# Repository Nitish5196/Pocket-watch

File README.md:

# Pocket Watch- KN
Its a mini pocket watch with a round display , a vibrating motor , a battery and a xiao esp32-C6 . and the best part? it charges wirelesslyyyyy
ikr so cool . so i designed the pcb in kicad , the case in fusion 360 and the firmware in vs code and ardunio ide oh about the firmware i forgot to tell you wht it does.
### Firmware:
- it has a deep sleep mode so most of the time its sleeping to conserve battery , it wakes up at when you shake it aggressively 
- when it turns on in the mrng and it broadcasts its own local wifi , you connect to it , open the webpage and a prompt pops up asking for day order or holiday
once you enter tht , it will show the tabular form of the time table of the day and sends a message to the watch and turns off
- during normal time the screen stays black and shows nothing , but you can shake to wake it up make it show the time and current/upcoming class.
- automatically 5mins before and at the start of the class it lights up and notifies you by turning on and vibrating
- Right before i leave for school it turns on and once i submit the day order the wifi turns off and it goes back to sleep
- THIS IS DESIGNED ACCORDING TO MY SCHOOL TIME TABLE SO YOU SHOULD PROBABLY MAKE CHANGES TO THE FIRMWARE IF YOU'RE PLANNING TO USE IT 
## PCB 

## Case (will make changes once the component's size are measured)

## BOM
## Bill of Materials (BOM)

| Part | Quantity | Total Cost(USD) | Vendor | Link |
|---|---:|---:|---|---|
| Flat 1034 Mobile Phone Vibrator Motor | 1 | $0.31 | Robu | [link](https://robu.in/product/flat-1027-mobile-phone-vibration-motor/) |
| STMicroelectronics LIS3DH 3-Axis Digital Accelerometer | 1 | $2.7 | Robocraze | [link](https://robocraze.com/products/7semi-lis3dh-triple-axis-mems-accelerometer-breakout-module-i2c-spi?variant=52662486434016) |
| GoldenMorning GC9A01P 1.28" 240×240 SPI Round Display | 1 | $5.06 | Robu | [link](https://robu.in/product/goldenmorning-gc9a01-7p-240x240-spi-1-28-inch-round-display-module/) |
| 2N2222 NPN Transistor | 5 | $0.12 | Robu | [link](https://robu.in/product/2n2222-npn-transistor-pack-of-20/) |
| 1kΩ 1W Metal Film Resistor | 6 | $0.13 | Robu | [link](https://robu.in/product/1k-ohm-1w-metal-film-resistor-pack-of-40/) |
| 1N4148 Small Signal Diode | 2 | $0.15 | Robu | [link](https://robu.in/product/1n4148-tap-vishay-1n4148-tap-small-signal-diode-single-100-v-150-ma-1-v-8-ns-2-a/) |
| Seeed Studio XIAO ESP32C3 | 1 | $6.4 | Robocraze | [link](https://robocraze.com/products/seeed-studio-xiao-esp32c3?variant=46039428366560) |
| 3.7V 300mAh LiPo Battery | 1  | $4 | Amazon | [link](https://www.amazon.in/gp/product/B0FGFK19DF/ref=ewc_pr_img_1?smid=A3QQB9C2QXM7ZJ&psc=1) |
| Power/kill Switch | 1 | $0.2 | robu | [link](https://robu.in/product-category/slide-switches/)| 
| Custom PCB | 1 | $10.5 | Lion Circuits | [link](https://www.lioncircuits.com/quote) |
| 3d Case | 2 | $7| Printing legion  | [join Hack Club!!](https://printlegion.hackclub.com/)|
| **TOTAL** | | **$37.6** | (incl shipping:$1)| |

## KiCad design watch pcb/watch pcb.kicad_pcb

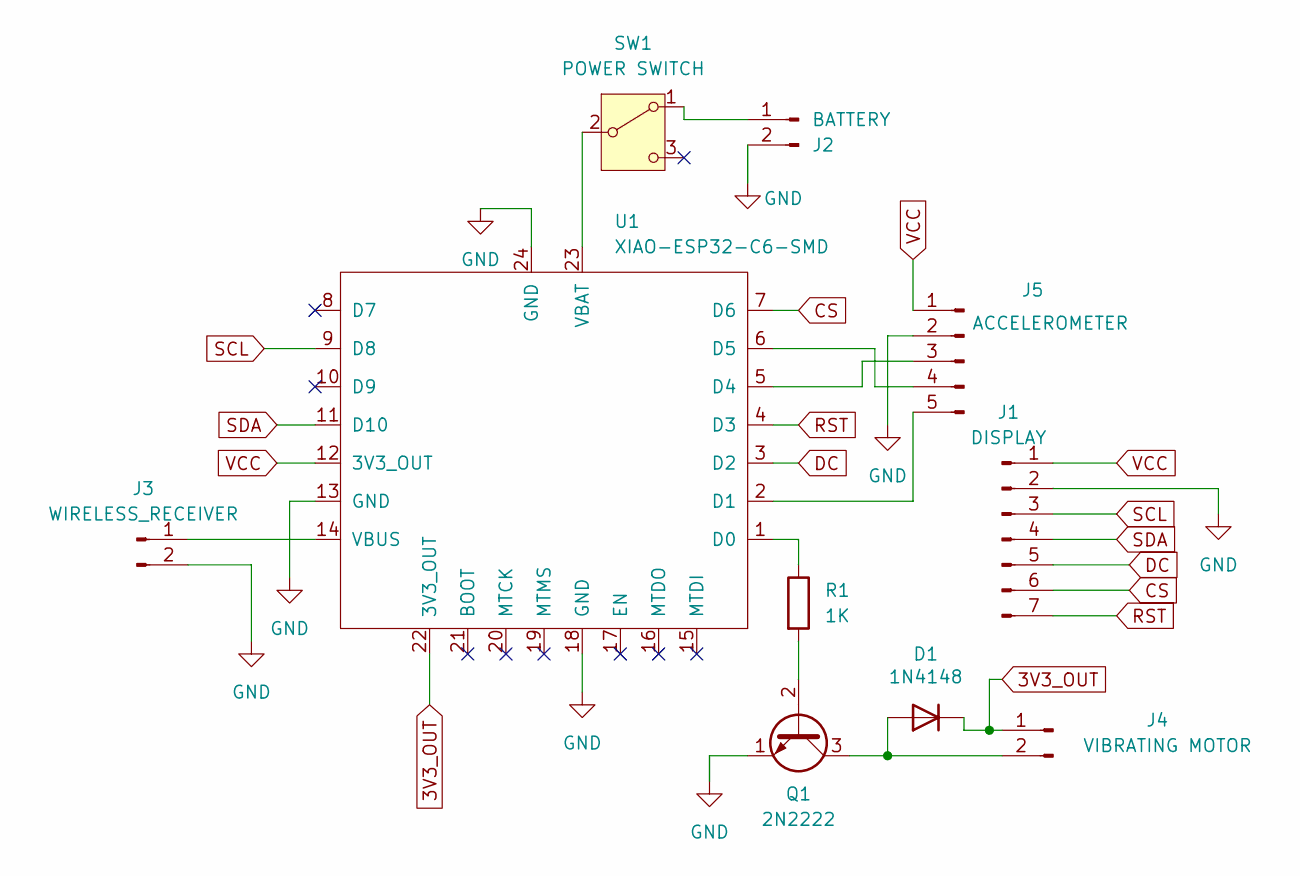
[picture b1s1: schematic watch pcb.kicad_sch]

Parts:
D1: 1N4148; D_DO-35_SOD27_P7.62mm_Horizontal
J1: DISPLAY; PinHeader_1x07_P2.54mm_Vertical
J2: BATTERY; PinHeader_1x02_P2.54mm_Vertical
J3: WIRELESS_RECEIVER; PinHeader_1x02_P2.54mm_Vertical
J4: VIBRATING MOTOR; PinHeader_1x02_P2.54mm_Vertical
J5: ACCELEROMETER; PinHeader_1x05_P2.54mm_Vertical
Q1: 2N2222; TO-92_Inline
R1: 1K; R_0805_2012Metric
SW1: POWER SWITCH; SW_DPDT_CK_JS202011JCQN
U1: XIAO-ESP32-C6-SMD

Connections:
3V3_OUT: D1.1 (K), J4.1, U1.22 (3V3_OUT)
CS: J1.6, U1.7 (D6)
DC: J1.5, U1.3 (D2)
GND: J1.2, J2.2, J3.2, J5.2, Q1.1 (E), U1.13 (GND), U1.18 (GND), U1.24 (GND)
unnamed: D1.2 (A), J4.2, Q1.3 (C)
unnamed: J2.1, SW1.1 (A)
unnamed: J3.1, U1.14 (VBUS)
unnamed: J5.3, U1.5 (D4)
unnamed: J5.4, U1.6 (D5)
unnamed: J5.5, U1.2 (D1)
unnamed: Q1.2 (B), R1.2
unnamed: SW1.2 (B), U1.23 (VBAT)
unnamed: R1.1, U1.1 (D0)
RST: J1.7, U1.4 (D3)
SCL: J1.3, U1.9 (D8)
SDA: J1.4, U1.11 (D10)
VCC: J1.1, J5.1, U1.12 (3V3_OUT)

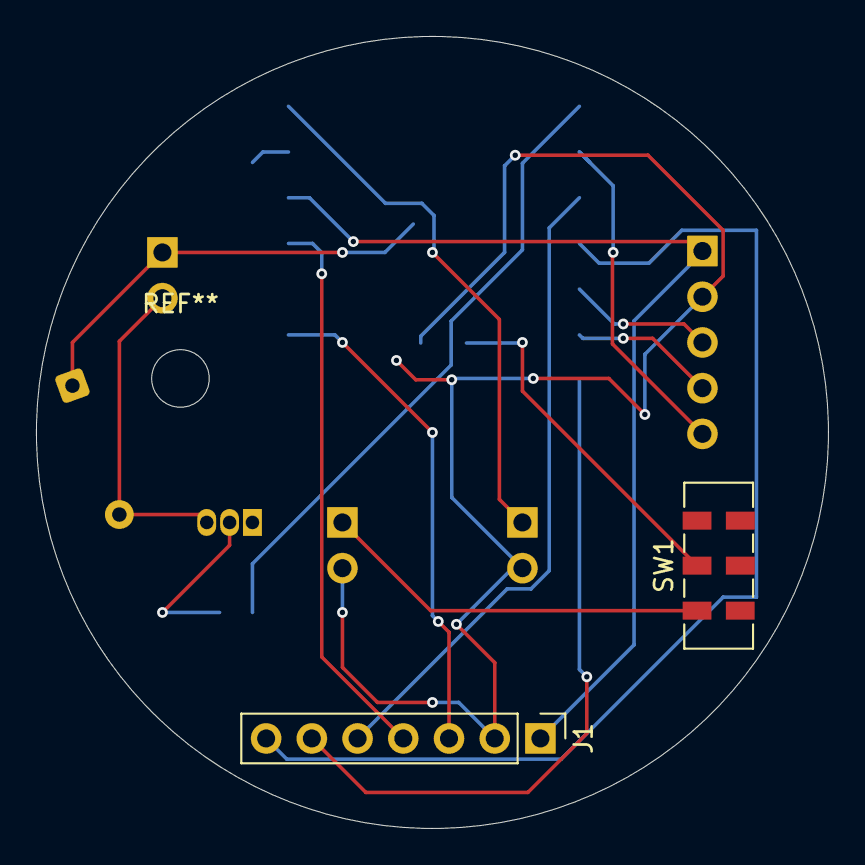
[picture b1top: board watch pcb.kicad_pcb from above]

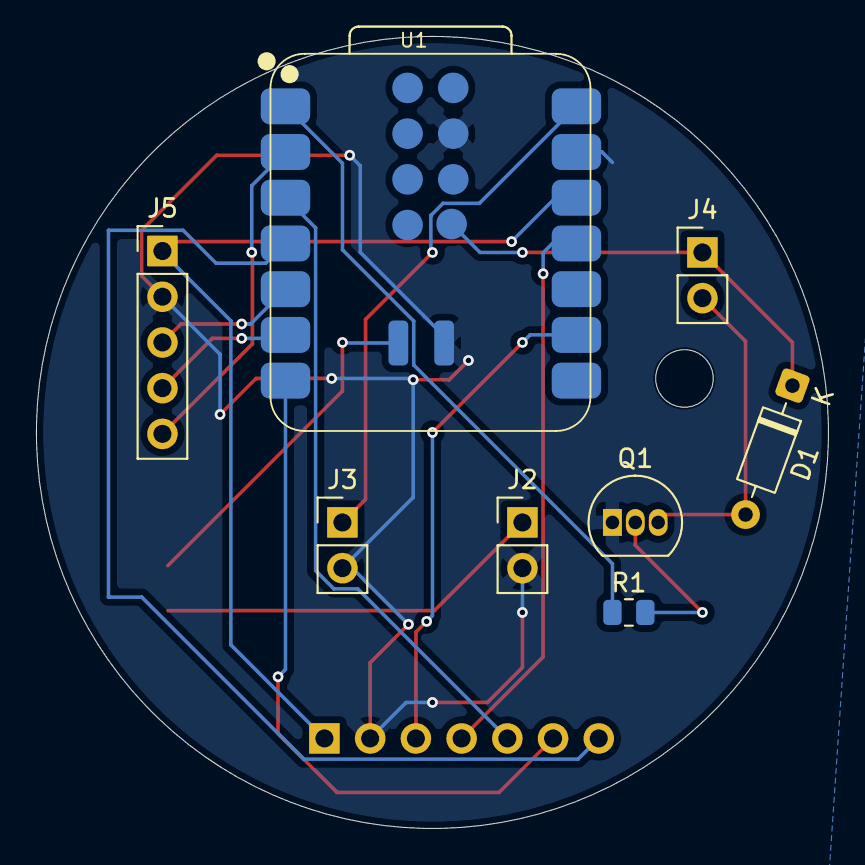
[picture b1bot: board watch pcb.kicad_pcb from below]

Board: 2 copper layers, 44.0 x 44.0 mm, 10 parts (8 on the bottom side), 17 nets.

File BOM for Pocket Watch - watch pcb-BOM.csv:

Id,Designator,Footprint,Quantity,Designation,Supplier and ref,Price
1,D1,D_DO-35_SOD27_P7.62mm_Horizontal,1,1N4148,https://robu.in/product/1n4148-tap-vishay-1n4148-tap-small-s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,$0.15
2,J1,PinHeader_1x07_P2.54mm_Vertical,1,DISPLAY,https://robu.in/product/goldenmorning-gc9a01-7p-240x240-spi-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,$5.06
3,J2,PinHeader_1x02_P2.54mm_Vertical,1,BATTERY,https://www.amazon.in/gp/product/B0DY89KG26/ref=ox_sc_saved_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,$3.80
4,J3,PinHeader_1x02_P2.54mm_Vertical,1,WIRELESS_RECEIVER,https://www.amazon.in/gp/product/B0FN4J4VNT/ref=ox_sc_act_ti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,$5.97
5,J4,PinHeader_1x02_P2.54mm_Vertical,1,VIBRATING MOTOR,https://robu.in/product/flat-1027-mobile-phone-vibration-motor/,$0.31
6,J5,PinHeader_1x05_P2.54mm_Vertical,1,ACCELEROMETER,https://robu.in/product/smartelex-triple-axis-accelerometer-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,$2.80
7,Q1,TO-92_Inline,1,2N2222,https://robu.in/product/2n2222-npn-transistor-pack-of-20/,$0.12
8,R1,R_0805_2012Metric,1,1K,https://robu.in/product/1k-ohm-1w-metal-film-resistor-pack-of-40/,$0.13
9,SW1,SW_DPDT_CK_JS202011JCQN,1,POWER SWITCH,https://robu.in/product-category/slide-switches/,$0.20
10,U1,XIAO-ESP32-C6-SMD,1,XIAO-ESP32-C6-SMD,https://robu.in/product/seeed-studio-xiao-esp32c6/,$10.33
